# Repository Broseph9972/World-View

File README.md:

# World-View
World View is a wall-mounted LED map built from one controller and 45 identical display tiles.

## Hardware (KiCad 10)

- [Controller project](hardware/controller/WorldView%20Controller.kicad_pro): Pico W, rotary encoder inputs, and five buffered row outputs.
- [Tile project](hardware/tile/WorldView%20Tile.kicad_pro): one 8 × 8 LED board, repeated nine times per row across five rows.
- [Shared symbols](hardware/shared/MapParts.kicad_sym): the project-local library used by both projects.

Open the `.kicad_pro` for the board you want, then launch its schematic or PCB editor from the KiCad project manager.

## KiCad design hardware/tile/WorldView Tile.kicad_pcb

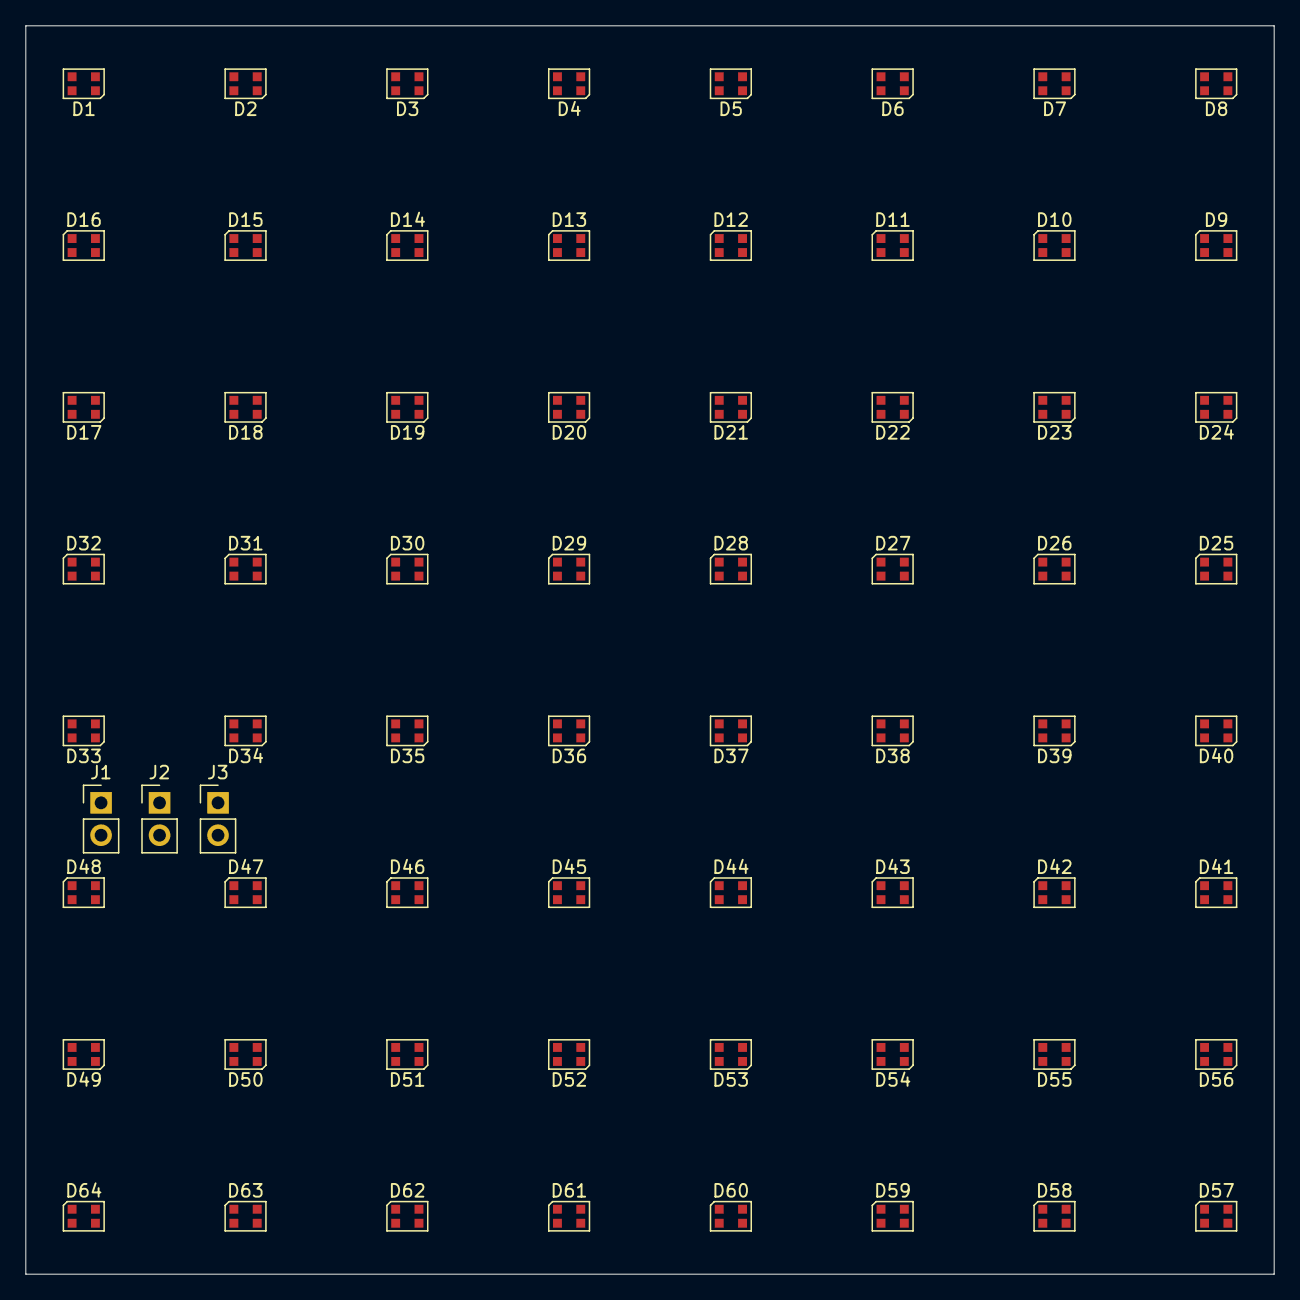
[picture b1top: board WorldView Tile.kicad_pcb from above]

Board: 2 copper layers, 98.0 x 98.0 mm, 67 parts (0 on the bottom side), 67 nets, no tracks yet.

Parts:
D1, D2, D3, D4, D5, D6, D7, D8, D9, D10, D11, D12, D13, D14, D15, D16, D17, D18, D19, D20, D21, D22, D23, D24, D25, D26, D27, D28, D29, D30, D31, D32, D33, D34, D35, D36, D37, D38, D39, D40, D41, D42, D43, D44, D45, D46, D47, D48, D49, D50, D51, D52, D53, D54, D55, D56, D57, D58, D59, D60, D61, D62, D63, D64: WS2812B-2020; LED_WS2812B-2020_PLCC4_2.0x2.0mm
J1: J1; PinHeader_1x02_P2.54mm_Vertical
J2: J2; PinHeader_1x02_P2.54mm_Vertical
J3: J3; PinHeader_1x02_P2.54mm_Vertical

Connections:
/5V: D1.4 (VDD), D2.4 (VDD), D3.4 (VDD), D4.4 (VDD), D5.4 (VDD), D6.4 (VDD), D7.4 (VDD), D8.4 (VDD), D9.4 (VDD), D10.4 (VDD), D11.4 (VDD), D12.4 (VDD), D13.4 (VDD), D14.4 (VDD), D15.4 (VDD), D16.4 (VDD), D17.4 (VDD), D18.4 (VDD), D19.4 (VDD), D20.4 (VDD), D21.4 (VDD), D22.4 (VDD), D23.4 (VDD), D24.4 (VDD), D25.4 (VDD), D26.4 (VDD), D27.4 (VDD), D28.4 (VDD), D29.4 (VDD), D30.4 (VDD), D31.4 (VDD), D32.4 (VDD), D33.4 (VDD), D34.4 (VDD), D35.4 (VDD), D36.4 (VDD), D37.4 (VDD), D38.4 (VDD), D39.4 (VDD), D40.4 (VDD), D41.4 (VDD), D42.4 (VDD), D43.4 (VDD), D44.4 (VDD), D45.4 (VDD), D46.4 (VDD), D47.4 (VDD), D48.4 (VDD), D49.4 (VDD), D50.4 (VDD), D51.4 (VDD), D52.4 (VDD), D53.4 (VDD), D54.4 (VDD), D55.4 (VDD), D56.4 (VDD), D57.4 (VDD), D58.4 (VDD), D59.4 (VDD), D60.4 (VDD), D61.4 (VDD), D62.4 (VDD), D63.4 (VDD), D64.4 (VDD), J3.1
/DIN: D1.3 (DIN), J1.1
/DOUT: D64.1 (DOUT), J2.1
/GND: D1.2 (VSS), D2.2 (VSS), D3.2 (VSS), D4.2 (VSS), D5.2 (VSS), D6.2 (VSS), D7.2 (VSS), D8.2 (VSS), D9.2 (VSS), D10.2 (VSS), D11.2 (VSS), D12.2 (VSS), D13.2 (VSS), D14.2 (VSS), D15.2 (VSS), D16.2 (VSS), D17.2 (VSS), D18.2 (VSS), D19.2 (VSS), D20.2 (VSS), D21.2 (VSS), D22.2 (VSS), D23.2 (VSS), D24.2 (VSS), D25.2 (VSS), D26.2 (VSS), D27.2 (VSS), D28.2 (VSS), D29.2 (VSS), D30.2 (VSS), D31.2 (VSS), D32.2 (VSS), D33.2 (VSS), D34.2 (VSS), D35.2 (VSS), D36.2 (VSS), D37.2 (VSS), D38.2 (VSS), D39.2 (VSS), D40.2 (VSS), D41.2 (VSS), D42.2 (VSS), D43.2 (VSS), D44.2 (VSS), D45.2 (VSS), D46.2 (VSS), D47.2 (VSS), D48.2 (VSS), D49.2 (VSS), D50.2 (VSS), D51.2 (VSS), D52.2 (VSS), D53.2 (VSS), D54.2 (VSS), D55.2 (VSS), D56.2 (VSS), D57.2 (VSS), D58.2 (VSS), D59.2 (VSS), D60.2 (VSS), D61.2 (VSS), D62.2 (VSS), D63.2 (VSS), D64.2 (VSS), J1.2, J2.2, J3.2
/P1: D1.1 (DOUT), D2.3 (DIN)
/P2: D2.1 (DOUT), D3.3 (DIN)
/P3: D3.1 (DOUT), D4.3 (DIN)
/P4: D4.1 (DOUT), D5.3 (DIN)
/P5: D5.1 (DOUT), D6.3 (DIN)
/P6: D6.1 (DOUT), D7.3 (DIN)
/P7: D7.1 (DOUT), D8.3 (DIN)
/P8: D8.1 (DOUT), D9.3 (DIN)
/P9: D9.1 (DOUT), D10.3 (DIN)
/P10: D10.1 (DOUT), D11.3 (DIN)
/P11: D11.1 (DOUT), D12.3 (DIN)
/P12: D12.1 (DOUT), D13.3 (DIN)
/P13: D13.1 (DOUT), D14.3 (DIN)
/P14: D14.1 (DOUT), D15.3 (DIN)
/P15: D15.1 (DOUT), D16.3 (DIN)
/P16: D16.1 (DOUT), D17.3 (DIN)
/P17: D17.1 (DOUT), D18.3 (DIN)
/P18: D18.1 (DOUT), D19.3 (DIN)
/P19: D19.1 (DOUT), D20.3 (DIN)
/P20: D20.1 (DOUT), D21.3 (DIN)
/P21: D21.1 (DOUT), D22.3 (DIN)
/P22: D22.1 (DOUT), D23.3 (DIN)
/P23: D23.1 (DOUT), D24.3 (DIN)
/P24: D24.1 (DOUT), D25.3 (DIN)
/P25: D25.1 (DOUT), D26.3 (DIN)
/P26: D26.1 (DOUT), D27.3 (DIN)
/P27: D27.1 (DOUT), D28.3 (DIN)
/P28: D28.1 (DOUT), D29.3 (DIN)
/P29: D29.1 (DOUT), D30.3 (DIN)
/P30: D30.1 (DOUT), D31.3 (DIN)
/P31: D31.1 (DOUT), D32.3 (DIN)
/P32: D32.1 (DOUT), D33.3 (DIN)
/P33: D33.1 (DOUT), D34.3 (DIN)
/P34: D34.1 (DOUT), D35.3 (DIN)
/P35: D35.1 (DOUT), D36.3 (DIN)
/P36: D36.1 (DOUT), D37.3 (DIN)
/P37: D37.1 (DOUT), D38.3 (DIN)
/P38: D38.1 (DOUT), D39.3 (DIN)
/P39: D39.1 (DOUT), D40.3 (DIN)
/P40: D40.1 (DOUT), D41.3 (DIN)
/P41: D41.1 (DOUT), D42.3 (DIN)
/P42: D42.1 (DOUT), D43.3 (DIN)
/P43: D43.1 (DOUT), D44.3 (DIN)
/P44: D44.1 (DOUT), D45.3 (DIN)
/P45: D45.1 (DOUT), D46.3 (DIN)
/P46: D46.1 (DOUT), D47.3 (DIN)
/P47: D47.1 (DOUT), D48.3 (DIN)
/P48: D48.1 (DOUT), D49.3 (DIN)
/P49: D49.1 (DOUT), D50.3 (DIN)
/P50: D50.1 (DOUT), D51.3 (DIN)
/P51: D51.1 (DOUT), D52.3 (DIN)
/P52: D52.1 (DOUT), D53.3 (DIN)
/P53: D53.1 (DOUT), D54.3 (DIN)
/P54: D54.1 (DOUT), D55.3 (DIN)
/P55: D55.1 (DOUT), D56.3 (DIN)
/P56: D56.1 (DOUT), D57.3 (DIN)
/P57: D57.1 (DOUT), D58.3 (DIN)
/P58: D58.1 (DOUT), D59.3 (DIN)
/P59: D59.1 (DOUT), D60.3 (DIN)
/P60: D60.1 (DOUT), D61.3 (DIN)
/P61: D61.1 (DOUT), D62.3 (DIN)
/P62: D62.1 (DOUT), D63.3 (DIN)
/P63: D63.1 (DOUT), D64.3 (DIN)
